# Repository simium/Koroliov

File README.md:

Koroliov
========

Flight hardware and software for the Koroliov SSDV project.

Modules used in this version:
* Arduino Micro: http://arduino.cc/en/Main/arduinoBoardMicro
* Radiometrix NTX2: http://www.radiometrix.com/content/ntx2
* TTL Serial JPEG Camera: https://www.adafruit.com/product/397
* Altitude/Pressure/Temperature sensor - MPL3115A2: https://www.sparkfun.com/products/11084
* MicroSD card breakout: https://www.adafruit.com/products/254

Future modules that could be added:
* Radiometrix NTX2B: http://www.radiometrix.com/content/ntx2b
* Adafruit's Ultimate GPS: https://www.adafruit.com/products/746

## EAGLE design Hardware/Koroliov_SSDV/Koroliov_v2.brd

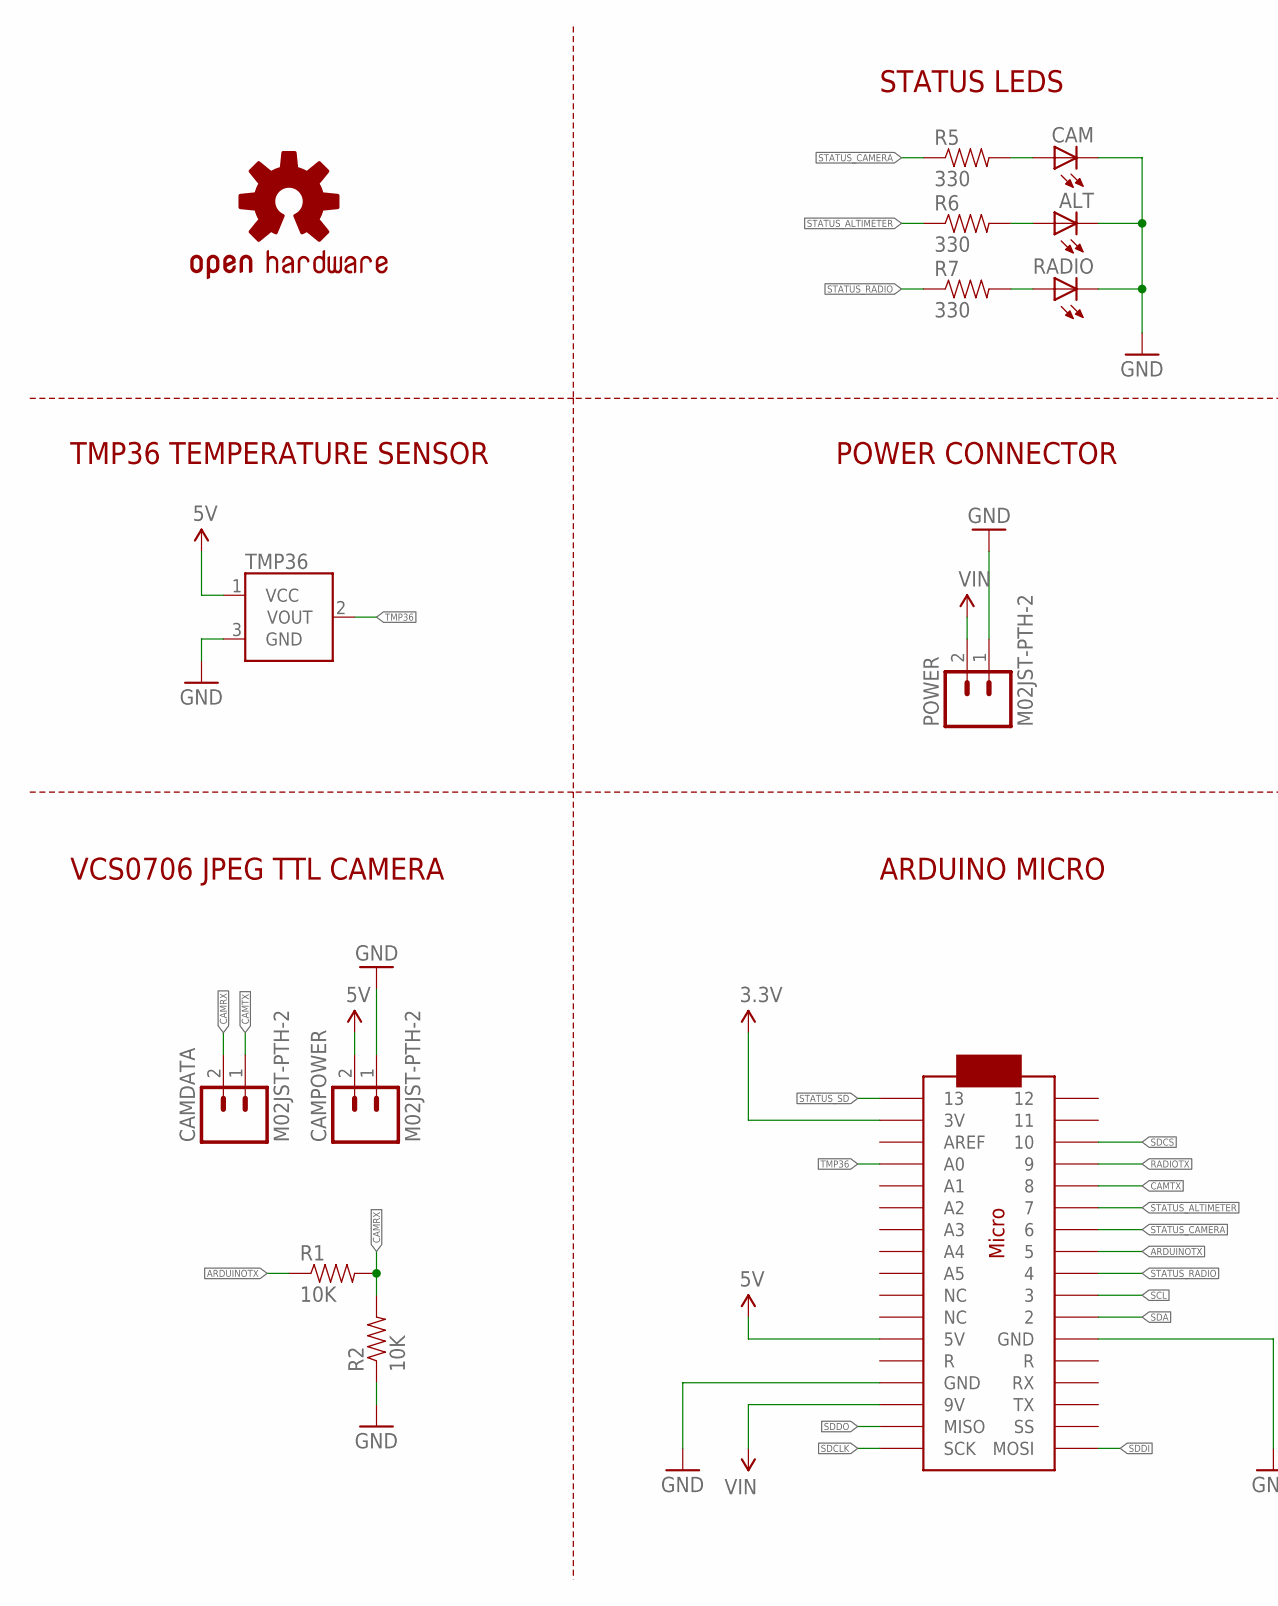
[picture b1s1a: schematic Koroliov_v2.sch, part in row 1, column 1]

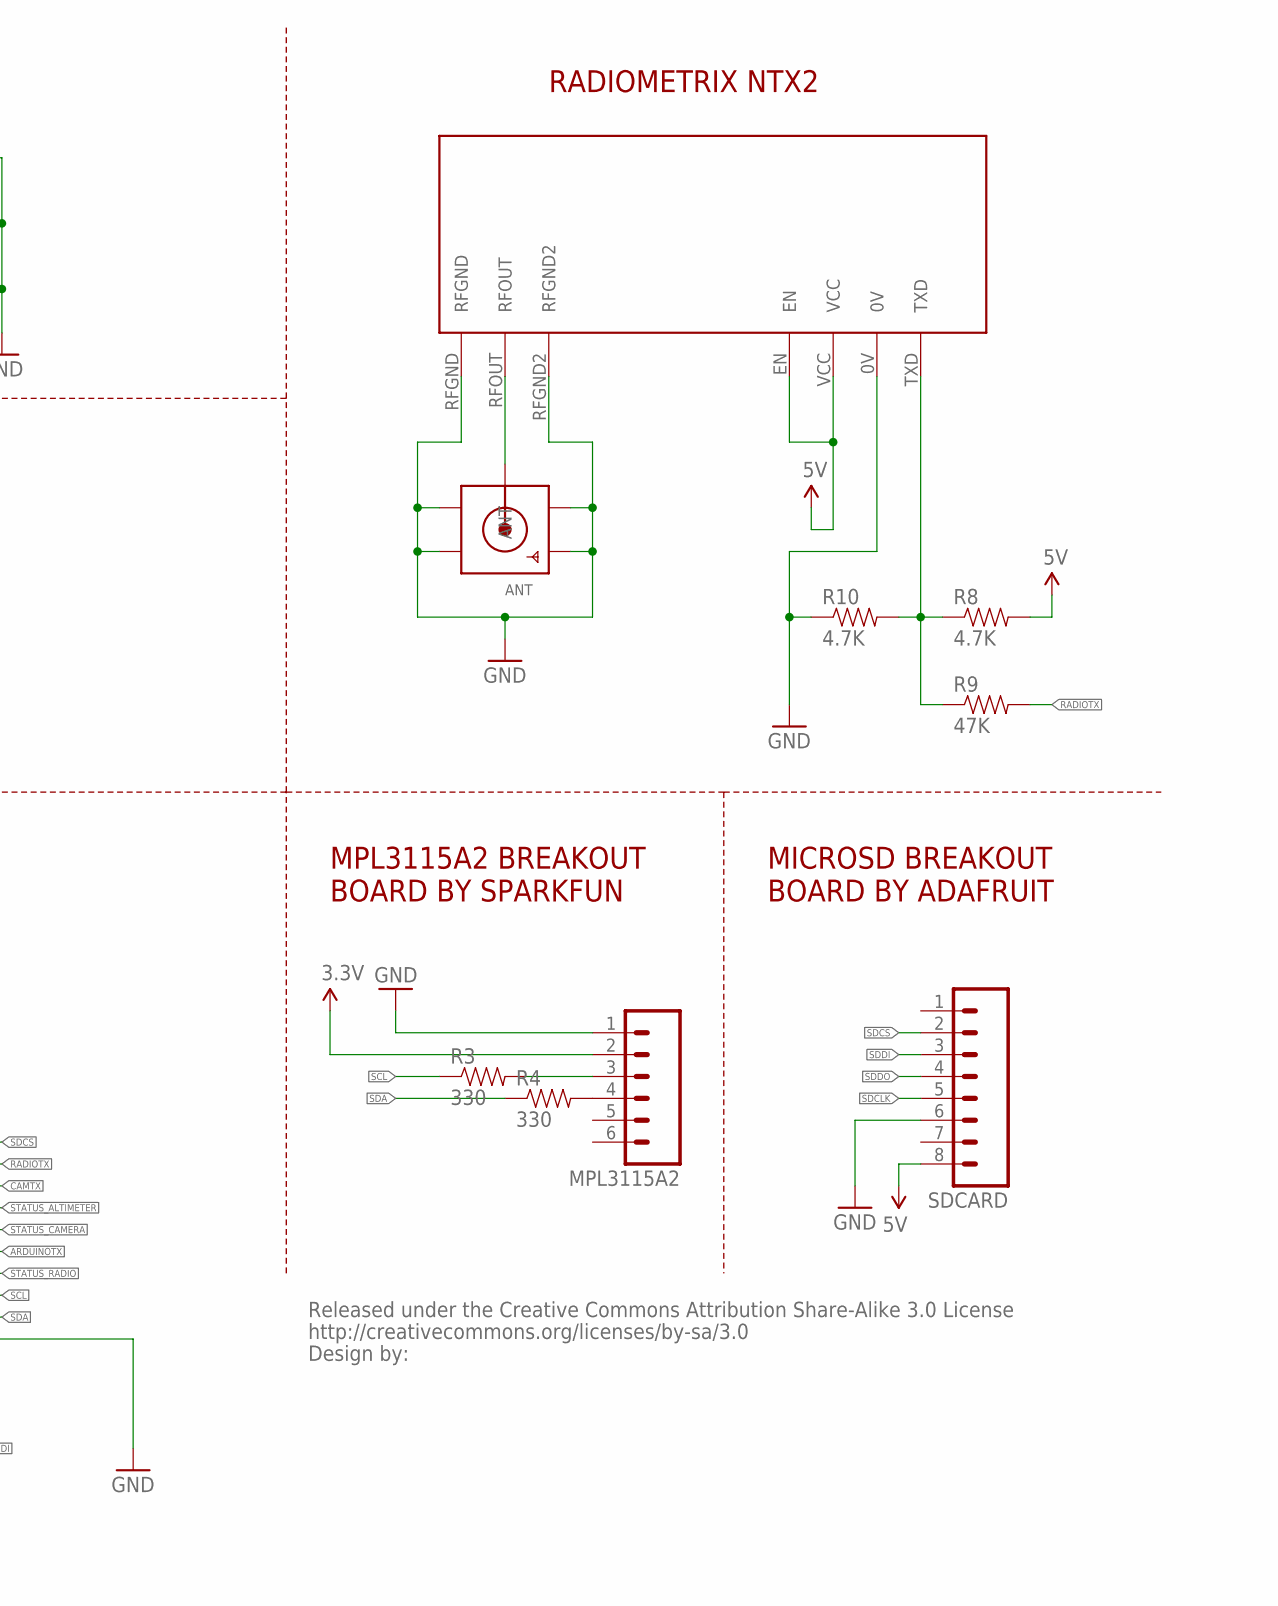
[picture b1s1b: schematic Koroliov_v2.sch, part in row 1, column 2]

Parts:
ALT: LED1206; LED-1206
ANT: SMACONNECTOR_EDGE; SMA_EDGELAUNCH
ARDUINOMICRO: ARDUINOMICRO
CAM: LED1206; LED-1206
CAMDATA: M02JST-PTH-2; JST-2-PTH
CAMPOWER: M02JST-PTH-2; JST-2-PTH
CC_TEXT1: CREATIVE_COMMONS
LOGO1: OSHW-LOGOL; OSHW-LOGO-L
MPL3115A2: M06SIP; 1X06
NTX2: NTX2
POWER: M02JST-PTH-2; JST-2-PTH
R1, R2: 10K; 1206
R3, R4, R5, R6, R7: 330; 1206
R8, R10: 4.7K; 1206
R9: 47K; 1206
RADIO: LED1206; LED-1206
SDCARD: M081X08; 1X08
TMP36: TMP36GT9; TO-92

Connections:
3.3V: ARDUINOMICRO.P$33 (3V), MPL3115A2.2
5V: ARDUINOMICRO.P$23 (5V), CAMPOWER.2, NTX2.EN, NTX2.VCC, R8.2, SDCARD.8, TMP36.1 (VCC)
ARDUINOTX: ARDUINOMICRO.P$8 (5), R1.1
CAMRX: CAMDATA.2, R1.2, R2.2
CAMTX: ARDUINOMICRO.P$5 (8), CAMDATA.1
GND: ALT.C, ANT.GND@1 (GND4), ANT.GND@2 (GND3), ANT.GND@3 (GND2), ANT.GND@4 (GND1), ARDUINOMICRO.P$12 (GND), ARDUINOMICRO.P$21 (GND), CAM.C, CAMPOWER.1, MPL3115A2.1, NTX2.0V, NTX2.RFGND, NTX2.RFGND2, POWER.1, R2.1, R10.1, RADIO.C, SDCARD.6, TMP36.3 (GND)
unnamed: ANT.P (ANT), NTX2.RFOUT
unnamed: CAM.A, R5.2
unnamed: ALT.A, R6.2
unnamed: MPL3115A2.3, R3.2
unnamed: MPL3115A2.4, R4.2
unnamed: R7.2, RADIO.A
unnamed: NTX2.TXD, R8.1, R9.1, R10.2
RADIOTX: ARDUINOMICRO.P$4 (9), R9.2
SCL: ARDUINOMICRO.P$10 (3), R3.1
SDA: ARDUINOMICRO.P$11 (2), R4.1
SDCLK: ARDUINOMICRO.P$18 (SCK), SDCARD.5
SDCS: ARDUINOMICRO.P$3 (10), SDCARD.2
SDDI: ARDUINOMICRO.P$17 (MOSI), SDCARD.3
SDDO: ARDUINOMICRO.P$19 (MISO), SDCARD.4
STATUS_ALTIMETER: ARDUINOMICRO.P$6 (7), R6.1
STATUS_CAMERA: ARDUINOMICRO.P$7 (6), R5.1
STATUS_RADIO: ARDUINOMICRO.P$9 (4), R7.1
STATUS_SD: ARDUINOMICRO.P$34 (13)
TMP36: ARDUINOMICRO.P$31 (A0), TMP36.2 (VOUT)
VIN: ARDUINOMICRO.P$20 (9V), POWER.2

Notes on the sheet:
MPL3115A2 BREAKOUT BOARD BY SPARKFUN
MICROSD BREAKOUT BOARD BY ADAFRUIT
RADIOMETRIX NTX2
ARDUINO MICRO
STATUS LEDS
POWER CONNECTOR
TMP36 TEMPERATURE SENSOR
VCS0706 JPEG TTL CAMERA

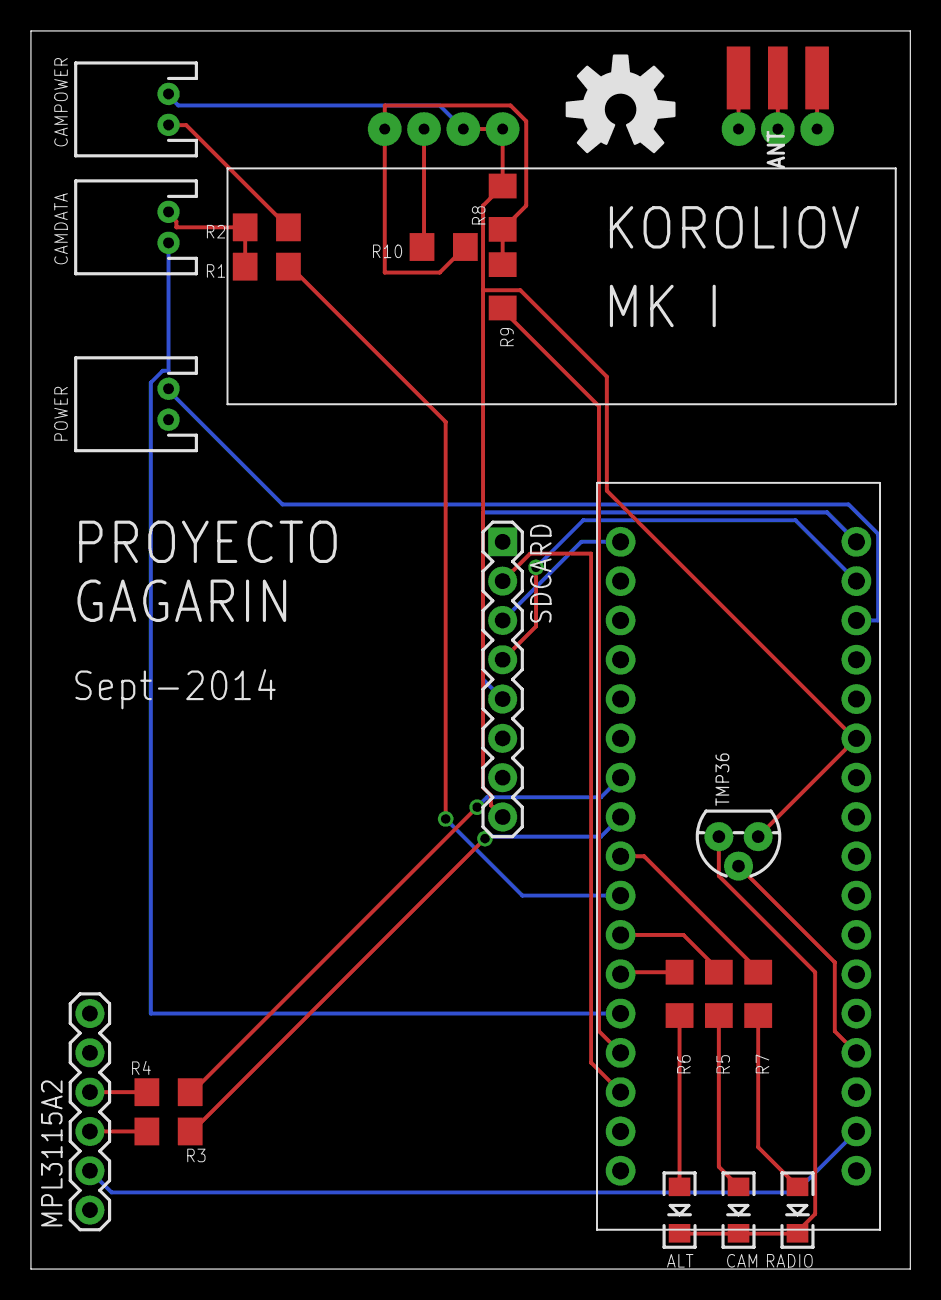
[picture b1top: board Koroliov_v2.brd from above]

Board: 2 copper layers, 56.8 x 80.0 mm, 24 parts (0 on the bottom side), 25 nets.

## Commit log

2014-07-29 First commit of the hardware
    This is the board currently sent to fabrication.
2014-08-25 Fixes after first fabrication
    Arduino Micro was not fully compatible with previous layout for the
    camera and the SD card. Antenna SMA connector has been moved to edge for
    better connection with antenna cable.
2014-08-25 Main hardware test for telemetry
    If you can decode this telemetry you should be good to go and can move
    on to test SSDV.
2014-08-25 Updated README.
    Updated README with hardware information.
2014-08-26 RTTY and SSDV work!
    Finally, stable @ 50 bps.
2014-08-29 RTTY and SSDV finally at 300 bps
    Works flawlessly. Current code keeps the camera sending images for 4
    hours with only 6 AA batteries, thinking how to optimize radio use.
2014-09-04 RTTY, SSDV and GPS at 300 baud
    I2C device removed, added GPS. Everything is being fine tuned.
2014-09-04 Flight code for mission Tereshkova 2
    Whatever will be, will be :D

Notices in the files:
parts and their libraries:
SparkFun-Connectors: Licensing: CC v3.0 Share-Alike You are welcome to use this library for commercial purposes.
SparkFun-Aesthetics: Released under the Creative Commons Attribution Share-Alike 3.0 License
SparkFun-Aesthetics: http://creativecommons.org/licenses/by-sa/3.0
